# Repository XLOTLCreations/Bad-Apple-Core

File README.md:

Project Disclaimer and Overview

- This project has been designed by me with the sole obsession of trying to run the infamous 'Bad Apple' video (so the name) as resourcefully with least computational power as one can compared to a previous project (with relatively much more computation and features, titled 'Bad Apple' original) therefore boiling it down to it's only 'Core' aspect of video playback and from scratch without any references to any existing similar projects anywhere. All the documentation (including this one) is compiled and handwritten with outmost human accuracy without the help of AI, with that said the included Arduino test sketches and Python script are with the AI help.

- This doc helps the reader navigate through documents to develop/mod, verify and manufacture this project from start to finish. Project files include Schematic, PCB Layout and reference pictures to recreate my setup and my results, for which adhering to the highlighted sequence of steps in respective areas is highly advised. 

- For the ones who received this project from me as a gift, please ignore Doc1 and proceed with Doc2, as Doc1 strictly talks about virgin boot of this board and only requires to be done once per board.

- Project is open source software and hardware, please refer the included ECAD files for hardware insight. To my fellow hardware design engineers and experts, any design improvement suggestions are more than welcome. For the ones not so learned in the ways of hardware, may this project enlighten you with some new knowledge that you can take home. 

🎯 Project Specifications:
I am listing basic specifications for someone to decide here itself if they are interested in continuing further. No soldering required. Please note that project was designed with the intention of learning for new comers/beginners, do not @me for something the project was clearly not meant to achieve which is complexity and obscurity. Intended for kids learning in school, present it at your 'show and tell', tell me how it goes.

Connections: USB-C (Full-Speed), ICSP header (no-fit),\
Main Processor: Atmega32U4,\
Human Machine Interface: 4x tactile buttons for interaction (active LOW),\
Output: 12x9 Charlie Plexed LED Matrix driven using IS31FL3731-QF over I2C,\
Storage: W25Q128JVP 16MByte QSPI NOR Flash (video frames, game assets),\
System Working Voltage: Vsys=3.3V,\
System Clock: 8MHz,\
(over-clocking/over-volting not advised)

- Lastly, this project has no version or revision history (call me lucky to have gotten everything right the first time itself) and has an elder project by the name 'Bad Apple' which was reduced down to it's core functionality hence the reasoning behind naming this second project as 'Bad Apple Core'. Please refer to that project with several advancements and higher complexity, if not up yet then stay tuned as the project is ready and working, I am busy documenting it.

HAVE FUN LEARNING - PLAYING - EXPERIMENTING - DEVELOPING.............

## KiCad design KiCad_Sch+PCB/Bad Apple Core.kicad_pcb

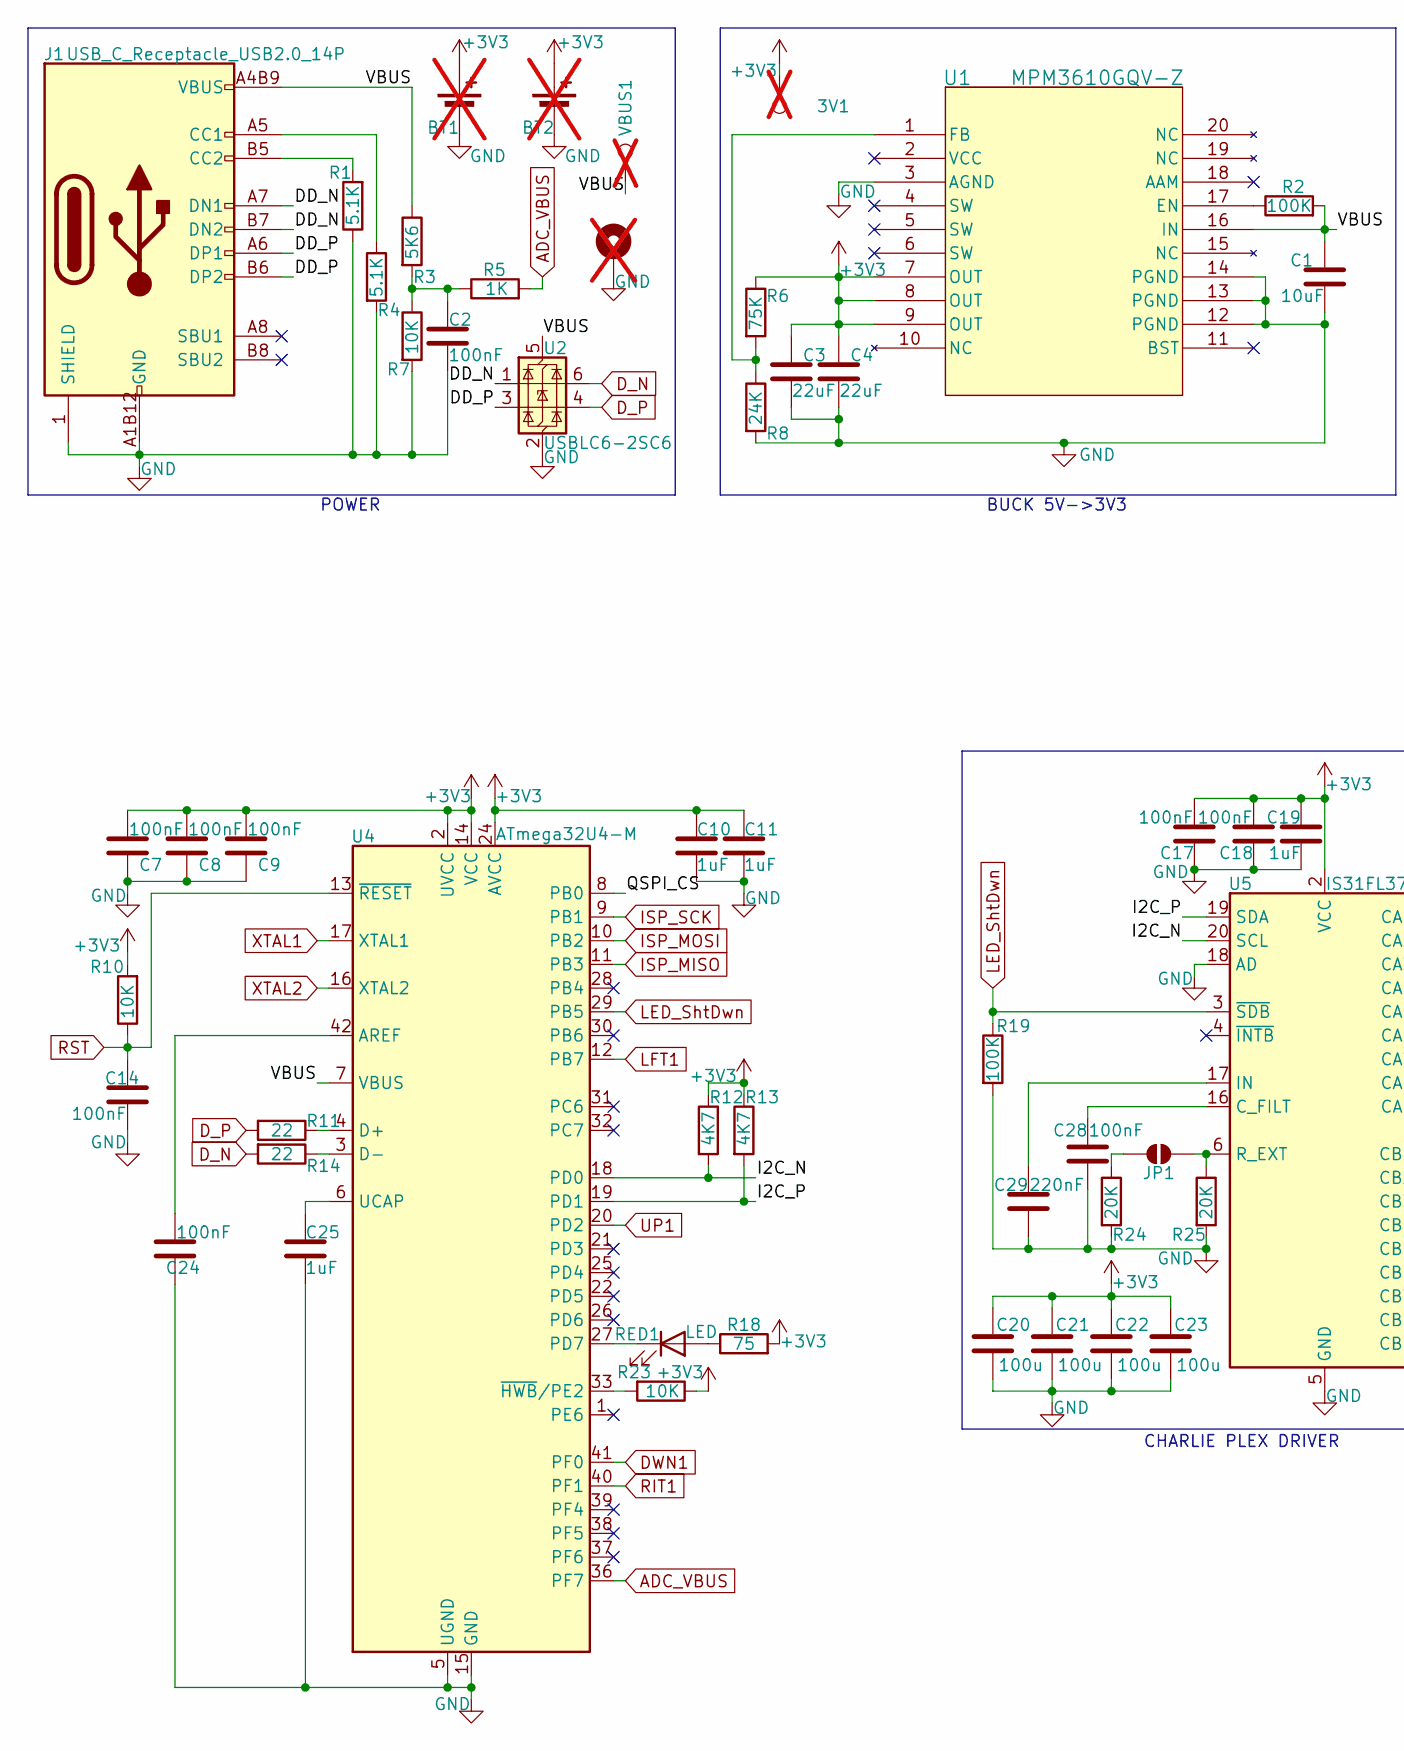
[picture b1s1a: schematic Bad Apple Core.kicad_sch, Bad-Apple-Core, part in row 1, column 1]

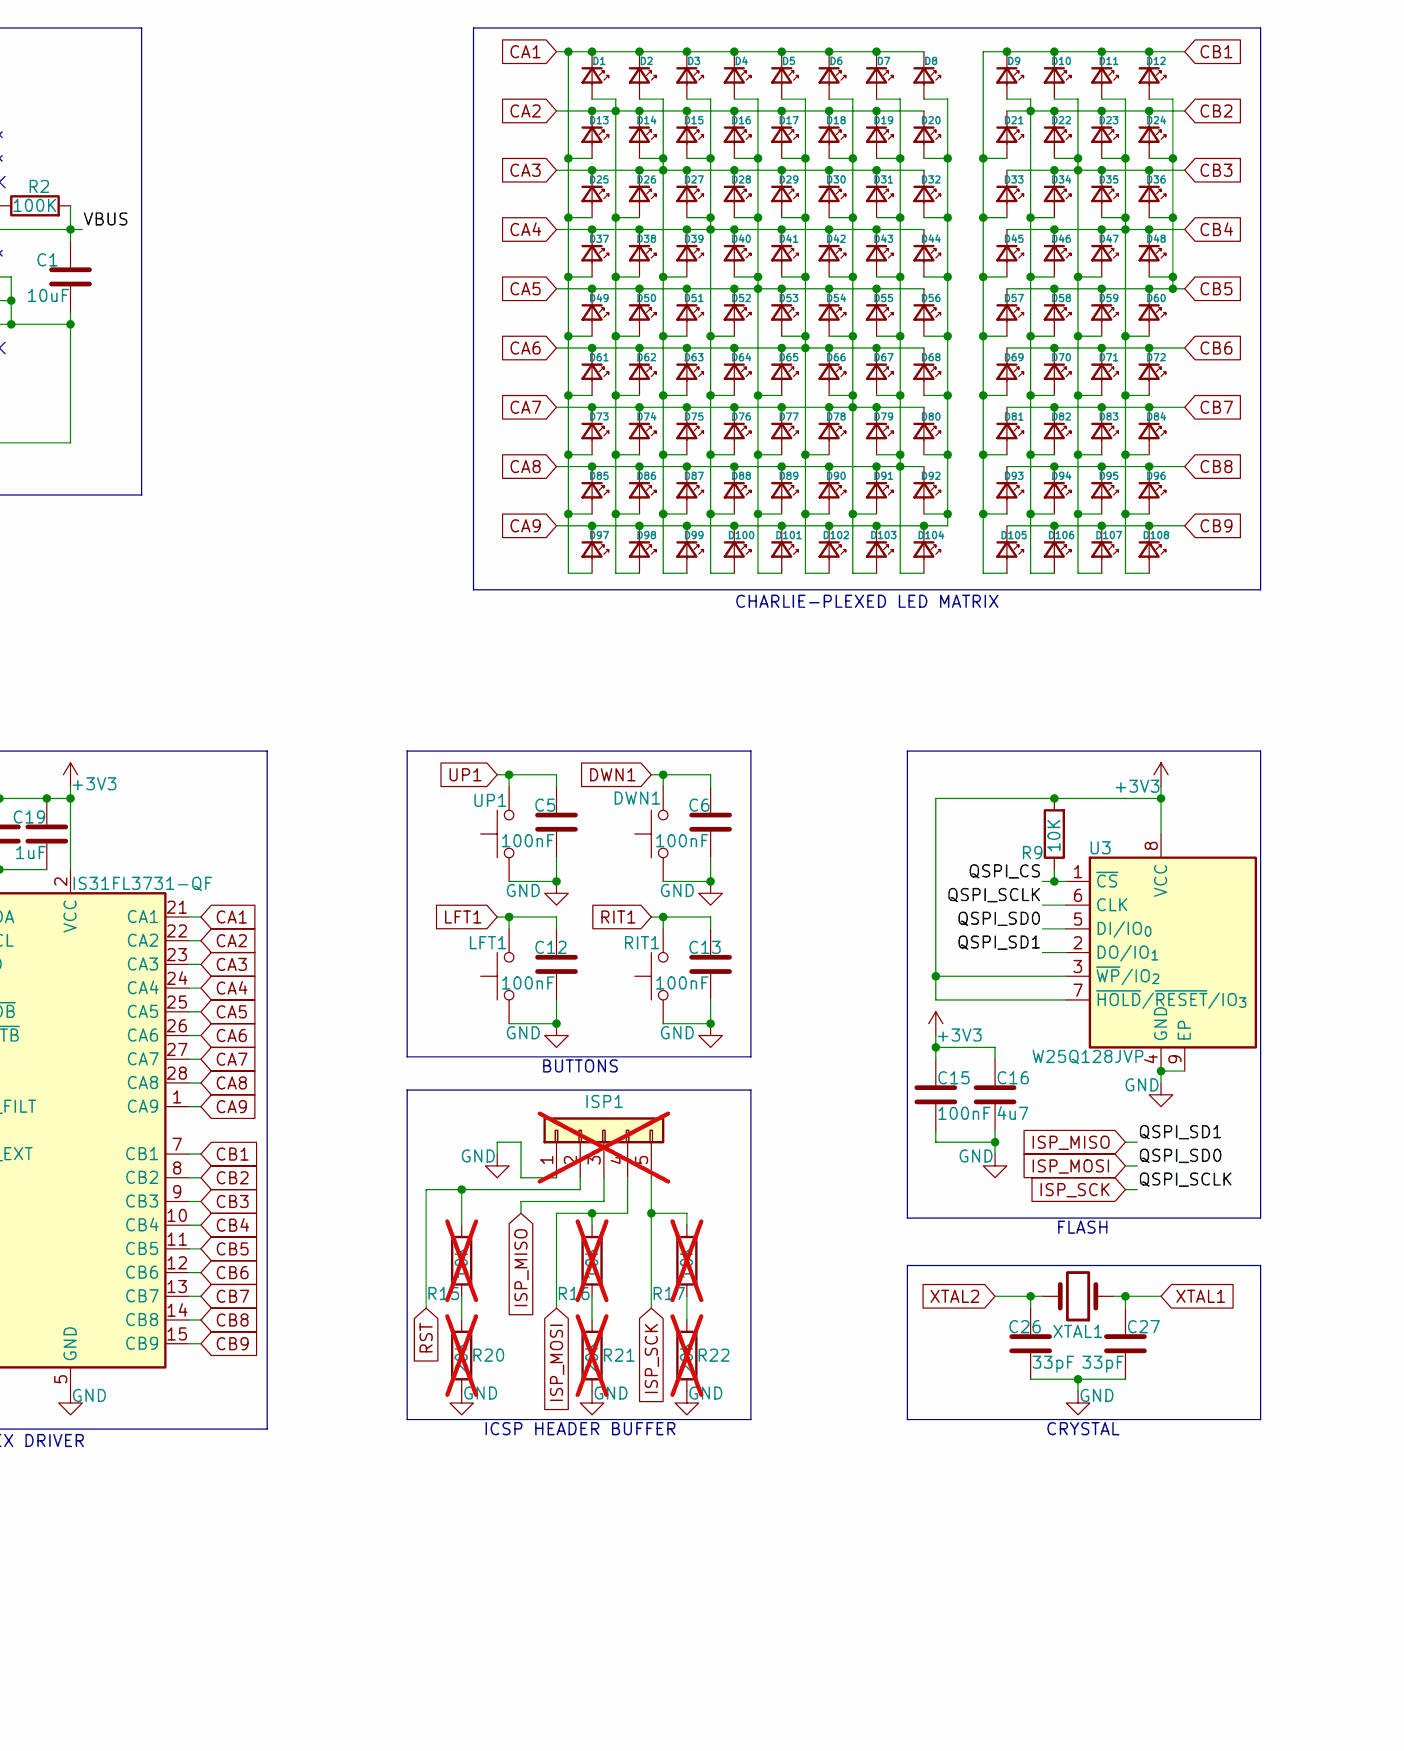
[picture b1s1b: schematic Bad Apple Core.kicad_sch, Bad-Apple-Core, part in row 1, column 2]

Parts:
3V1: TestPoint; TestPoint_Pad_D1.0mm; not fitted
BT1: Battery_Cell; BatteryHolder_Multicomp_BC-2001_1x2032; not fitted
BT2: Battery_Cell; BatteryHolder_Keystone_3008_1x2450; not fitted
C1: 10uF; C_0603_1608Metric; JLCPCB# C19702
C2, C5, C6, C7, C8, C9, C12, C13, C14, C15, C17, C18, C24, C28: 100nF; C_0402_1005Metric; JLCPCB# C1525
C3, C4: 22uF; C_0805_2012Metric; JLCPCB# C45783
C10, C11, C19, C25: 1uF; C_0402_1005Metric; JLCPCB# C52923
C16: 4u7; C_0402_1005Metric; JLCPCB# C23733
C20, C21, C22, C23: 100u; C_1206_3216Metric; JLCPCB# C15008
C26, C27: 33pF; C_0402_1005Metric; JLCPCB# C1562
C29: 220nF; C_0402_1005Metric; JLCPCB# C16772
D1, D2, D3, D4, D5, D6, D7, D8, D9, D10, D11, D12, D13, D14, D15, D16, D17, D18, D19, D20, D21, D22, D23, D24, D25, D26, D27, D28, D29, D30, D31, D32, D33, D34, D35, D36, D37, D38, D39, D40, D41, D42, D43, D44, D45, D46, D47, D48, D49, D50, D51, D52, D53, D54, D55, D56, D57, D58, D59, D60, D61, D62, D63, D64, D65, D66, D67, D68, D69, D70, D71, D72, D73, D74, D75, D76, D77, D78, D79, D80, D81, D82, D83, D84, D85, D86, D87, D88, D89, D90, D91, D92, D93, D94, D95, D96, D97, D98, D99, D100, D101, D102, D103, D104, D105, D106, D107, D108: LED_Small; LED_0603_1608Metric; JLCPCB# C2290
DWN1: SW_Push; PushButton_4x3mm_Custom; JLCPCB# C720477
H1: MountingHole_Pad; MountingHole_2.7mm_M2.5_DIN965_Pad; JLCPCB# N/A; not fitted
ISP1: Conn_01x05; PinHeader_1x05_P2.00mm_Vertical; not fitted
J1: USB_C_Receptacle_USB2.0_14P; USB-C_Custom; JLCPCB# C2927037
JP1: SolderJumper_2_Open; SolderJumper-2_P1.3mm_Open_Pad1.0x1.5mm
LFT1: SW_Push; PushButton_4x3mm_Custom; JLCPCB# C720477
R1, R4: 5.1K; R_0402_1005Metric; JLCPCB# C25905
R2, R19: 100K; R_0402_1005Metric; JLCPCB# C25741
R3: 5K6; R_0603_1608Metric; JLCPCB# C23189
R5: 1K; R_0402_1005Metric; JLCPCB# C11702
R6: 75K; R_0603_1608Metric; JLCPCB# C23242
R7: 10K; R_0603_1608Metric; JLCPCB# C25804
R8: 24K; R_0603_1608Metric; JLCPCB# C23352
R9, R10, R23: 10K; R_0402_1005Metric; JLCPCB# C25744
R11, R14: 22; R_0402_1005Metric; JLCPCB# C25092
R12, R13: 4K7; R_0402_1005Metric; JLCPCB# C25900
R15, R16, R17: 10K; R_0402_1005Metric; JLCPCB# C25744; not fitted
R18: 75; R_0603_1608Metric; JLCPCB# C4275
R20, R21, R22: 20K; R_0402_1005Metric; JLCPCB# C25765; not fitted
R24, R25: 20K; R_0402_1005Metric; JLCPCB# C25765
RED1: LED; LED_0603_1608Metric; JLCPCB# C2286
RIT1: SW_Push; PushButton_4x3mm_Custom; JLCPCB# C720477
U1: MPM3610GQV-Z; QFN3p0x5p0x1p6_MPM3610_MNP; JLCPCB# C5183856
U2: USBLC6-2SC6; SOT-23-6; JLCPCB# C7519
U3: W25Q128JVP; WSON-8-1EP_6x5mm_P1.27mm_EP3.4x4.3mm; JLCPCB# C190862
U4: ATmega32U4-M; QFN-44-1EP_7x7mm_P0.5mm_EP5.2x5.2mm; MFR.Part # ATMEGA32U4-MU; JLCPCB# C112161
U5: IS31FL3731-QF; QFN-28-1EP_4x4mm_P0.4mm_EP2.3x2.3mm; JLCPCB# C191206
UP1: SW_Push; PushButton_4x3mm_Custom; JLCPCB# C720477
VBUS1: TestPoint; TestPoint_Pad_D1.0mm; not fitted
XTAL1: Crystal; Crystal_SMD_5032-2Pin_5.0x3.2mm; JLCPCB# C115962

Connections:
+3V3: 3V1.1, BT1.1 (+), BT2.1 (+), C3.1, C4.1, C7.1, C8.1, C9.1, C10.1, C11.1, C15.1, C16.1, C17.1, C18.1, C19.1, C20.1, C21.1, C22.1, C23.1, R6.1, R9.2, R10.2, R12.1, R13.1, R18.2, R23.1, U1.7 (OUT), U1.8 (OUT), U1.9 (OUT), U3.3 (~WP/IO_{2}), U3.7 (~HOLD/~RESET/IO_{3}), U3.8 (VCC), U4.2 (UVCC), U4.14 (VCC), U4.24 (AVCC), U4.34 (VCC), U4.44 (AVCC), U5.2 (VCC)
/DD_N: J1.A7 (DN1), J1.B7 (DN2), U2.1 (I/O1)
/DD_P: J1.A6 (DP1), J1.B6 (DP2), U2.3 (I/O2)
/I2C_N: R12.2, U4.18 (PD0), U5.20 (SCL)
/I2C_P: R13.2, U4.19 (PD1), U5.19 (SDA)
/QSPI_CS: R9.1, U3.1 (~CS), U4.8 (PB0)
/VBUS: C1.1, J1.A4B9 (VBUS), J1.B4A9 (VBUS), R2.2, R3.1, U1.16 (IN), U2.5 (VBUS), U4.7 (VBUS), VBUS1.1
ADC_VBUS: R5.2, U4.36 (PF7)
CA1: D1.1 (K), D2.1 (K), D3.1 (K), D4.1 (K), D5.1 (K), D6.1 (K), D7.1 (K), D8.1 (K), D13.2 (A), D25.2 (A), D37.2 (A), D49.2 (A), D61.2 (A), D73.2 (A), D85.2 (A), D97.2 (A), U5.21 (CA1)
CA2: D1.2 (A), D13.1 (K), D14.1 (K), D15.1 (K), D16.1 (K), D17.1 (K), D18.1 (K), D19.1 (K), D20.1 (K), D26.2 (A), D38.2 (A), D50.2 (A), D62.2 (A), D74.2 (A), D86.2 (A), D98.2 (A), U5.22 (CA2)
CA3: D2.2 (A), D14.2 (A), D25.1 (K), D26.1 (K), D27.1 (K), D28.1 (K), D29.1 (K), D30.1 (K), D31.1 (K), D32.1 (K), D39.2 (A), D51.2 (A), D63.2 (A), D75.2 (A), D87.2 (A), D99.2 (A), U5.23 (CA3)
CA4: D3.2 (A), D15.2 (A), D27.2 (A), D37.1 (K), D38.1 (K), D39.1 (K), D40.1 (K), D41.1 (K), D42.1 (K), D43.1 (K), D44.1 (K), D52.2 (A), D64.2 (A), D76.2 (A), D88.2 (A), D100.2 (A), U5.24 (CA4)
CA5: D4.2 (A), D16.2 (A), D28.2 (A), D40.2 (A), D49.1 (K), D50.1 (K), D51.1 (K), D52.1 (K), D53.1 (K), D54.1 (K), D55.1 (K), D56.1 (K), D65.2 (A), D77.2 (A), D89.2 (A), D101.2 (A), U5.25 (CA5)
CA6: D5.2 (A), D17.2 (A), D29.2 (A), D41.2 (A), D53.2 (A), D61.1 (K), D62.1 (K), D63.1 (K), D64.1 (K), D65.1 (K), D66.1 (K), D67.1 (K), D68.1 (K), D78.2 (A), D90.2 (A), D102.2 (A), U5.26 (CA6)
CA7: D6.2 (A), D18.2 (A), D30.2 (A), D42.2 (A), D54.2 (A), D66.2 (A), D73.1 (K), D74.1 (K), D75.1 (K), D76.1 (K), D77.1 (K), D78.1 (K), D79.1 (K), D80.1 (K), D91.2 (A), D103.2 (A), U5.27 (CA7)
CA8: D7.2 (A), D19.2 (A), D31.2 (A), D43.2 (A), D55.2 (A), D67.2 (A), D79.2 (A), D85.1 (K), D86.1 (K), D87.1 (K), D88.1 (K), D89.1 (K), D90.1 (K), D91.1 (K), D92.1 (K), D104.2 (A), U5.28 (CA8)
CA9: D8.2 (A), D20.2 (A), D32.2 (A), D44.2 (A), D56.2 (A), D68.2 (A), D80.2 (A), D92.2 (A), D97.1 (K), D98.1 (K), D99.1 (K), D100.1 (K), D101.1 (K), D102.1 (K), D103.1 (K), D104.1 (K), U5.1 (CA9)
CB1: D9.1 (K), D10.1 (K), D11.1 (K), D12.1 (K), D21.2 (A), D33.2 (A), D45.2 (A), D57.2 (A), D69.2 (A), D81.2 (A), D93.2 (A), D105.2 (A), U5.7 (CB1)
CB2: D9.2 (A), D21.1 (K), D22.1 (K), D23.1 (K), D24.1 (K), D34.2 (A), D46.2 (A), D58.2 (A), D70.2 (A), D82.2 (A), D94.2 (A), D106.2 (A), U5.8 (CB2)
CB3: D10.2 (A), D22.2 (A), D33.1 (K), D34.1 (K), D35.1 (K), D36.1 (K), D47.2 (A), D59.2 (A), D71.2 (A), D83.2 (A), D95.2 (A), D107.2 (A), U5.9 (CB3)
CB4: D11.2 (A), D23.2 (A), D35.2 (A), D45.1 (K), D46.1 (K), D47.1 (K), D48.1 (K), D60.2 (A), D72.2 (A), D84.2 (A), D96.2 (A), D108.2 (A), U5.10 (CB4)
CB5: D12.2 (A), D24.2 (A), D36.2 (A), D48.2 (A), D57.1 (K), D58.1 (K), D59.1 (K), D60.1 (K), U5.11 (CB5)
CB6: D69.1 (K), D70.1 (K), D71.1 (K), D72.1 (K), U5.12 (CB6)
CB7: D81.1 (K), D82.1 (K), D83.1 (K), D84.1 (K), U5.13 (CB7)
CB8: D93.1 (K), D94.1 (K), D95.1 (K), D96.1 (K), U5.14 (CB8)
CB9: D105.1 (K), D106.1 (K), D107.1 (K), D108.1 (K), U5.15 (CB9)
DWN1: C6.1, DWN1.1, U4.41 (PF0)
D_N: R14.2, U2.6 (I/O1)
D_P: R11.2, U2.4 (I/O2)
GND: BT1.2 (-), BT2.2 (-), C1.2, C2.2, C3.2, C4.2, C5.2, C6.2, C7.2, C8.2, C9.2, C10.2, C11.2, C12.2, C13.2, C14.2, C15.2, C16.2, C17.2, C18.2, C19.2, C20.2, C21.2, C22.2, C23.2, C24.2, C25.2, C26.2, C27.2, C28.2, C29.2, DWN1.2, H1.1, ISP1.1, J1.1 (SHIELD), J1.2 (SHIELD), J1.3 (SHIELD), J1.4 (SHIELD), J1.A1B12 (GND), J1.B1A12 (GND), LFT1.1, R1.1, R4.2, R7.2, R8.2, R19.2, R20.1, R21.1, R22.1, R24.2, R25.2, RIT1.1, U1.3 (AGND), U1.12 (PGND), U1.13 (PGND), U1.14 (PGND), U2.2 (GND), U3.4 (GND), U3.9 (EP), U4.5 (UGND), U4.15 (GND), U4.23 (GND), U4.35 (GND), U4.43 (GND), U4.45 (GND), U5.5 (GND), U5.18 (AD), U5.29 (GND), UP1.1
ISP_MISO: ISP1.3, U3.2 (DO/IO_{1}), U4.11 (PB3)
ISP_MOSI: ISP1.4, R16.2, U3.5 (DI/IO_{0}), U4.10 (PB2)
ISP_SCK: ISP1.5, R17.2, U3.6 (CLK), U4.9 (PB1)
LED_ShtDwn: R19.1, U4.29 (PB5), U5.3 (~SDB)
LFT1: C12.1, LFT1.2, U4.12 (PB7)
unnamed: C2.1, R3.2, R5.1, R7.1
unnamed: J1.A5 (CC1), R4.1
unnamed: J1.B5 (CC2), R1.2
unnamed: JP1.1 (A), R24.1
unnamed: JP1.2 (B), R25.1, U5.6 (R_EXT)
unnamed: R15.1, R20.2
unnamed: R16.1, R21.2
unnamed: R17.1, R22.2
unnamed: R18.1, RED1.2 (A)
unnamed: RED1.1 (K), U4.27 (PD7)
unnamed: R2.1, U1.17 (EN)
unnamed: R6.2, R8.1, U1.1 (FB)
unnamed: C24.1, U4.42 (AREF)
unnamed: R11.1, U4.4 (D+)
unnamed: R14.1, U4.3 (D-)
unnamed: C25.1, U4.6 (UCAP)
unnamed: R23.2, U4.33 (~HWB/PE2)
unnamed: C28.1, U5.16 (C_FILT)
unnamed: C29.1, U5.17 (IN)
RIT1: C13.1, RIT1.2, U4.40 (PF1)
RST: C14.1, ISP1.2, R10.1, R15.2, U4.13 (~RESET)
UP1: C5.1, U4.20 (PD2), UP1.2
XTAL1: C27.1, U4.17 (XTAL1), XTAL1.1
XTAL2: C26.1, U4.16 (XTAL2), XTAL1.2

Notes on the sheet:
CHARLIE-PLEXED LED MATRIX
FLASH
ICSP HEADER BUFFER
CHARLIE PLEX DRIVER
BUTTONS
BUCK 5V->3V3
POWER
CRYSTAL

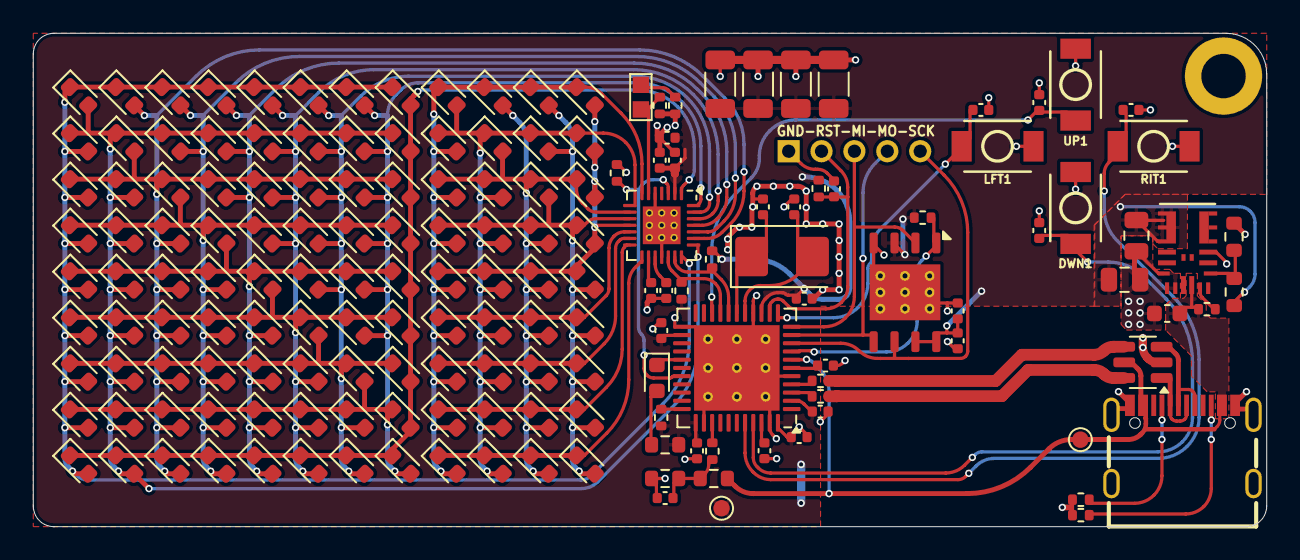
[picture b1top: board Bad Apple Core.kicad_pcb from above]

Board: 2 copper layers, 75.0 x 30.0 mm, 174 parts (1 on the bottom side), 56 nets.

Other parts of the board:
XLOTL CREATIONS: XLOTL Creations

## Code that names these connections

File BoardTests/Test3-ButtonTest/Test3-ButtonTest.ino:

/*
 * Button Test + VBUS Monitor
 * Tests 4 directional buttons and USB voltage monitoring
 * 
 * Buttons (Active LOW with 100nF debounce caps):
 * - Up:    D0  (PD2)
 * - Down:  A5  (PF0, ADC0)
 * - Right: A4  (PF1, ADC1)
 * - Left:  D11 (PB7)
 * 
 * VBUS Monitor: A0 (PF7, ADC7)
 * - Rtop=5.6K, Rbot=10K, 100nF filter, 1K series to ADC
 */

#include <Wire.h>
#include <Adafruit_GFX.h>
#include <Adafruit_IS31FL3731.h>

// Pin definitions
#define BTN_UP    0   // D0
#define BTN_DOWN  A5  // A5 (PF0)
#define BTN_RIGHT A4  // A4 (PF1)
#define BTN_LEFT  11  // D11
#define VBUS_MON  A0  // A0 (PF7, ADC7)
#define SDB_PIN   9   // IS31FL3731 shutdown

Adafruit_IS31FL3731 matrix = Adafruit_IS31FL3731();

void setup() {
  // Enable IS31FL3731
  pinMode(SDB_PIN, OUTPUT);
  digitalWrite(SDB_PIN, HIGH);
  delay(5);
  
  Serial.begin(115200);
  delay(2000);
  
  Serial.println("=== Button Test + VBUS Monitor ===");
  Serial.println();
  
  // Setup buttons with internal pull-ups (active LOW)
  pinMode(BTN_UP, INPUT_PULLUP);
  pinMode(BTN_DOWN, INPUT_PULLUP);
  pinMode(BTN_RIGHT, INPUT_PULLUP);
  pinMode(BTN_LEFT, INPUT_PULLUP);
  
  Serial.println("Buttons configured (active LOW with pull-ups)");
  Serial.println("- Up:    D0");
  Serial.println("- Down:  A5");
  Serial.println("- Right: A4");
  Serial.println("- Left:  D11");
  Serial.println();
  
  // Initialize LED matrix
  if (!matrix.begin(0x74)) {
    Serial.println("IS31FL3731 not found!");
    while (1);
  }
  
  matrix.clear();
  Serial.println("LED Matrix ready!");
  Serial.println();
  
  // Test VBUS monitoring
  Serial.println("=== VBUS Monitor Test ===");
  float vbus = readVBUS();
  Serial.print("USB Voltage: ");
  Serial.print(vbus);
  Serial.println(" V");
  
  if (vbus < 4.5) {
    Serial.println("⚠ WARNING: Low USB voltage detected!");
    Serial.println("  Consider dimming LEDs to prevent brownout");
  } else if (vbus > 5.5) {
    Serial.println("⚠ WARNING: High USB voltage!");
  } else {
    Serial.println("✓ USB voltage normal");
  }
  
  Serial.println();
  Serial.println("=== Button Test ===");
  Serial.println("Press buttons to see response!");
  Serial.println("Each button press will light up a direction arrow on the matrix");
  Serial.println();
}

// Read VBUS voltage
// Voltage divider: Rtop=5.6K, Rbot=10K
// Vout = Vin * (Rbot / (Rtop + Rbot))
// Vout = Vin * (10K / 15.6K) = Vin * 0.641
// Therefore: Vin = Vout / 0.641 = Vout * 1.560
float readVBUS() {
  int adcValue = analogRead(VBUS_MON);
  float vout = (adcValue / 1023.0) * 3.3; // ADC reading to voltage
  float vin = vout * 1.560; // Voltage divider ratio
  return vin;
}

// Draw arrow on LED matrix
void drawArrow(char direction) {
  matrix.clear();
  
  switch(direction) {
    case 'U': // Up arrow
      matrix.drawPixel(6, 1, 200);
      matrix.drawPixel(5, 2, 200);
      matrix.drawPixel(6, 2, 200);
      matrix.drawPixel(7, 2, 200);
      matrix.drawPixel(6, 3, 200);
      matrix.drawPixel(6, 4, 200);
      matrix.drawPixel(6, 5, 200);
      break;
      
    case 'D': // Down arrow
      matrix.drawPixel(6, 3, 200);
      matrix.drawPixel(6, 4, 200);
      matrix.drawPixel(6, 5, 200);
      matrix.drawPixel(6, 6, 200);
      matrix.drawPixel(5, 6, 200);
      matrix.drawPixel(6, 6, 200);
      matrix.drawPixel(7, 6, 200);
      matrix.drawPixel(6, 7, 200);
      break;
      
    case 'L': // Left arrow
      matrix.drawPixel(2, 4, 200);
      matrix.drawPixel(3, 3, 200);
      matrix.drawPixel(3, 4, 200);
      matrix.drawPixel(3, 5, 200);
      matrix.drawPixel(4, 4, 200);
      matrix.drawPixel(5, 4, 200);
      matrix.drawPixel(6, 4, 200);
      break;
      
    case 'R': // Right arrow
      matrix.drawPixel(5, 4, 200);
      matrix.drawPixel(6, 4, 200);
      matrix.drawPixel(7, 4, 200);
      matrix.drawPixel(8, 3, 200);
      matrix.drawPixel(8, 4, 200);
      matrix.drawPixel(8, 5, 200);
      matrix.drawPixel(9, 4, 200);
      break;
  }
}

void loop() {
  static unsigned long lastPrint = 0;
  static bool lastUp = HIGH;
  static bool lastDown = HIGH;
  static bool lastRight = HIGH;
  static bool lastLeft = HIGH;
  
  // Read buttons (active LOW, so LOW = pressed)
  bool up = digitalRead(BTN_UP);
  bool down = digitalRead(BTN_DOWN);
  bool right = digitalRead(BTN_RIGHT);
  bool left = digitalRead(BTN_LEFT);
  
  // Detect button press (transition from HIGH to LOW)
  if (up == LOW && lastUp == HIGH) {
    Serial.println("⬆ UP pressed");
    drawArrow('U');
  }
  if (down == LOW && lastDown == HIGH) {
    Serial.println("⬇ DOWN pressed");
    drawArrow('D');
  }
  if (right == LOW && lastRight == HIGH) {
    Serial.println("➡ RIGHT pressed");
    drawArrow('R');
  }
  if (left == LOW && lastLeft == HIGH) {
    Serial.println("⬅ LEFT pressed");
    drawArrow('L');
  }
  
  // Save button states
  lastUp = up;
  lastDown = down;
  lastRight = right;
  lastLeft = left;
  
  // Print VBUS voltage every 5 seconds
  if (millis() - lastPrint > 5000) {
    float vbus = readVBUS();
    Serial.print("VBUS: ");
    Serial.print(vbus);
    Serial.println(" V");
    lastPrint = millis();
  }
  
  delay(10); // Small delay for debouncing (hardware caps help too!)
}
